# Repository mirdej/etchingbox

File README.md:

# AETZBOX
### DIY Mobile PCB Etching KIT

## The Idea 
Build a portable / mobile PCB etching workstation that fulfills these criteria
* waterproof
* able to etch 100x160mm double sided boards with 8mil precision
* low cost.  total bill of materials should not exceed 150 CHF
* diy approach, mostly laser cut plexi and easily sourceable materials
* fits in a RAKO Box

Some guiding ideas
* use very little but always fresh chemicals 
* good heat management: etching has to be done at 45-50 degrees celsius, developer has to be kept at >20 degrees as well (in my workshop, temperatures can easily drop below 16 degrees and developing is a pain).
* all material and chemicals travel in the box. liquid waste can travel in the box as well until it can properly disposed of.
* should be easy to clean. no electronics exposed to moisture. 
* as few as possible switches and electrical contacts exposed to the harsh etching environment
* self illuminating

## More Info
https://wiki.sgmk-ssam.ch/index.php/EtchingBox

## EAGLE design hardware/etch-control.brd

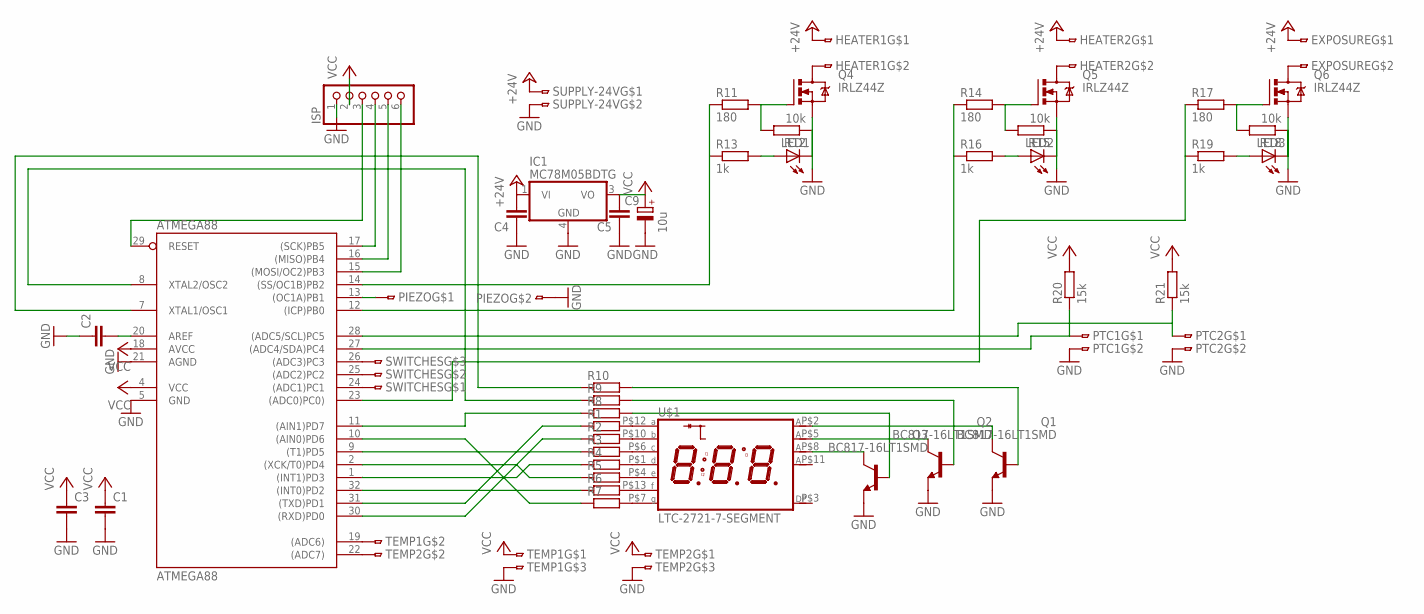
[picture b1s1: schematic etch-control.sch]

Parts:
ATMEGA88: ATMEGA88; TQFP32-08
C1, C2, C3, C4, C5: C-EUC0603; C0603
C9: 10u; CT3528
EXPOSURE: 2PIN-SMD-2.54
HEATER1, HEATER2: 2PIN-SMD-2.54
IC1: MC78M05BDTG; DPACK_3
ISP: PINHD-1X6; 1X06
LED1, LED2, LED3: LED3MM
PIEZO: 2PIN-SMD-2.54
PTC1, PTC2: 2PIN-SMD-2.54
Q1, Q2, Q3: BC817-16LT1SMD; SOT23-BEC
Q4, Q5, Q6: IRLZ44Z; TO220BH
R1, R2, R3, R4, R5, R6, R7, R8, R9, R10: R-EU_R1206; R1206
R11, R14, R17: 180; R1206
R12, R15, R18: 10k; R1206
R13, R16, R19: 1k; R1206
R20, R21: 15k; R1206
SUPPLY-24V: 2PIN-SMD-2.54
SWITCHES: 3PIN-SMD-2.54
TEMP1, TEMP2: 3PIN-SMD-2.54
U$1: LTC-2721-7-SEGMENT; LTC-2721

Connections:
+24V: C4.2, EXPOSURE.2, HEATER1.2, HEATER2.2, IC1.1 (VI), SUPPLY-24V.2
GND: ATMEGA88.5 (GND), ATMEGA88.21 (AGND), C1.2, C2.1, C3.2, C4.1, C5.1, C9.-, IC1.4 (GND), ISP.1, LED1.K (C), LED2.K (C), LED3.K (C), PIEZO.3, PTC1.3, PTC2.3, Q1.E, Q2.E, Q3.E, Q4.S, Q5.S, Q6.S, R12.1, R15.1, R18.1, SUPPLY-24V.3, TEMP1.3, TEMP2.3
MOSI: ATMEGA88.15 ((MOSI/OC2)PB3), ISP.6
unnamed: ATMEGA88.30 ((RXD)PD0), R2.1
unnamed: ATMEGA88.31 ((TXD)PD1), R1.1
unnamed: ATMEGA88.32 ((INT0)PD2), R6.1
unnamed: ATMEGA88.1 ((INT1)PD3), R4.1
unnamed: ATMEGA88.2 ((XCK/T0)PD4), R5.1
unnamed: ATMEGA88.8 (XTAL2/OSC2), R9.1
unnamed: ATMEGA88.7 (XTAL1/OSC1), R10.1
unnamed: ATMEGA88.11 ((AIN1)PD7), R8.1
unnamed: ATMEGA88.9 ((T1)PD5), R3.1
unnamed: R1.2, U$1.P$12 (A)
unnamed: R2.2, U$1.P$10 (B)
unnamed: R3.2, U$1.P$6 (C)
unnamed: R4.2, U$1.P$1 (D)
unnamed: R5.2, U$1.P$4 (E)
unnamed: R6.2, U$1.P$13 (F)
unnamed: R7.2, U$1.P$7 (G)
unnamed: ATMEGA88.29 (RESET), ISP.3
unnamed: ATMEGA88.20 (AREF), C2.2
unnamed: HEATER1.3, Q4.D
unnamed: Q4.G, R11.2, R12.2
unnamed: ATMEGA88.13 ((OC1A)PB1), PIEZO.2
unnamed: ATMEGA88.10 ((AIN0)PD6), R7.1
unnamed: LED1.A, R13.2
unnamed: ATMEGA88.14 ((SS/OC1B)PB2), R11.1, R13.1
unnamed: Q1.B, R10.2
unnamed: Q2.B, R9.2
unnamed: Q3.B, R8.2
unnamed: Q1.C, U$1.P$2 (D1)
unnamed: Q2.C, U$1.P$5 (D2)
unnamed: Q3.C, U$1.P$8 (D3)
unnamed: HEATER2.3, Q5.D
unnamed: Q5.G, R14.2, R15.2
unnamed: LED2.A, R16.2
unnamed: ATMEGA88.12 ((ICP)PB0), R14.1, R16.1
unnamed: EXPOSURE.3, Q6.D
unnamed: Q6.G, R17.2, R18.2
unnamed: LED3.A, R19.2
unnamed: ATMEGA88.16 ((MISO)PB4), ISP.5
unnamed: ATMEGA88.19 ((ADC6)), TEMP1.2
unnamed: ATMEGA88.22 ((ADC7)), TEMP2.2
unnamed: ATMEGA88.27 ((ADC4/SDA)PC4), PTC1.2, R20.1
unnamed: ATMEGA88.23 ((ADC0)PC0)), R17.1, R19.1
unnamed: ATMEGA88.28 ((ADC5/SCL)PC5), PTC2.2, R21.1
unnamed: ATMEGA88.24 ((ADC1)PC1), SWITCHES.1
unnamed: ATMEGA88.25 ((ADC2)PC2), SWITCHES.2
unnamed: ATMEGA88.26 ((ADC3)PC3), SWITCHES.3
SCK: ATMEGA88.17 ((SCK)PB5), ISP.4
VCC: ATMEGA88.4 (VCC), ATMEGA88.18 (AVCC), C1.1, C3.1, C5.2, C9.+, IC1.3 (VO), ISP.2, R20.2, R21.2, TEMP1.1, TEMP2.1

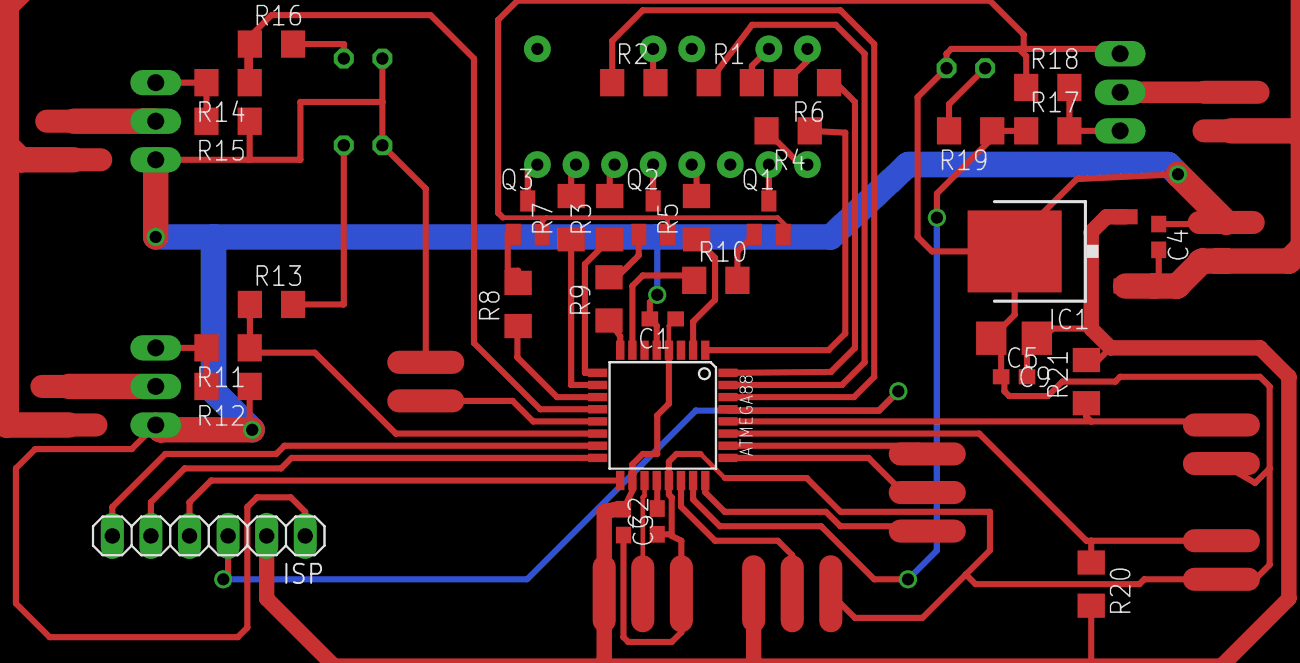
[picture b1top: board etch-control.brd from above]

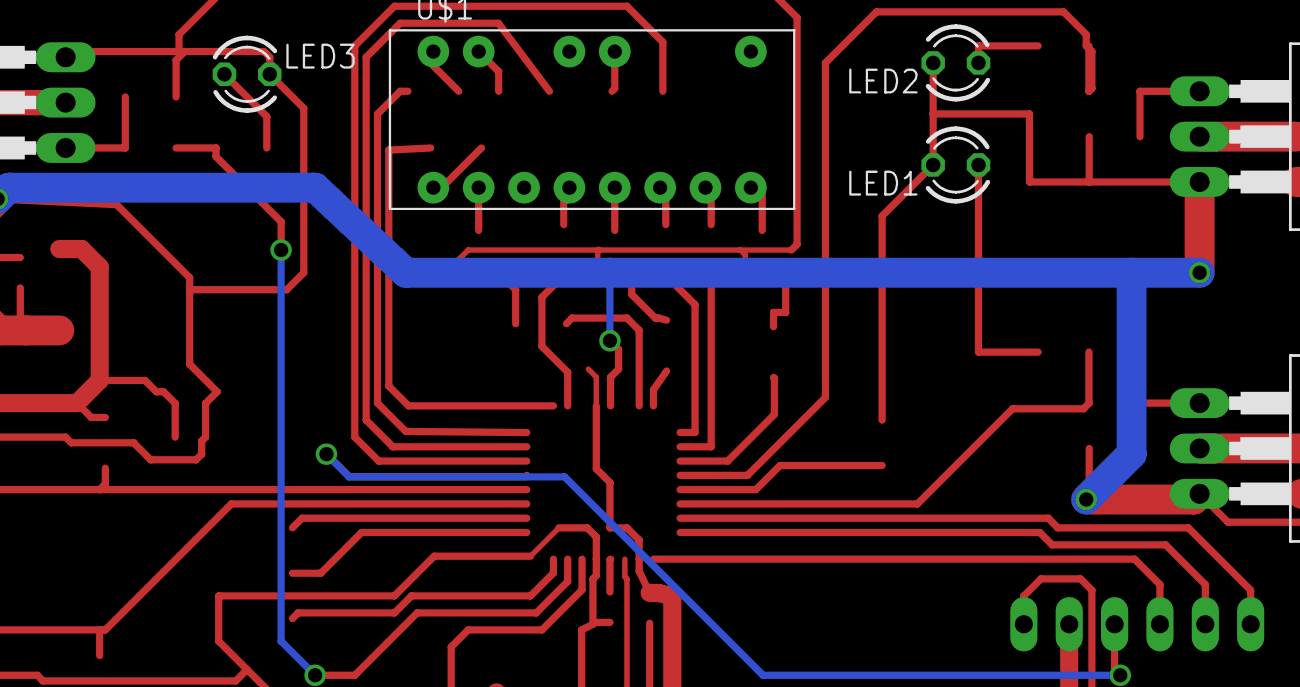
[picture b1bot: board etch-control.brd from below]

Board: 2 copper layers, 50 parts (7 on the bottom side), 51 nets.

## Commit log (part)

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2014-05-13 added readme
2014-05-13 redme
2014-05-13 added first version of controler pcb and firmware
2014-05-13 basic heater control
2018-11-13 make place for completely new version
2018-11-16 new approach
2018-11-16 change mosfets, smaller borad
2018-11-26 Basic fuctions
2018-11-26 add sketchup models
2018-11-29 new bubble unit, holes for china plugs
2018-11-30 new basin holder
2018-11-30 4mm smaller lightpad.
2018-11-30 correct uv height. lighter lid, text
2018-11-30 some corrections
2018-12-01 fix missing link
2018-12-02 small corrections to holes. logo
2018-12-02 forgot to add logo.h
2018-12-03 pimped display
2018-12-03 workshop photos
2018-12-04 some minor hardware corrections during workshop. seperate logos. merge display code by dusjagr. add ambient temperatur display
2018-12-04 add lid holder
2019-01-21 full stop uv when finished flashing. no ramp down
2019-02-08 add more sounds, temperature log option, safety check
2019-02-08 try pulsing airpump
2019-02-08 Using SAMD Timer 4 as slow PWM (crude way) to prevent whining of air pump
2019-02-09 add bath temperture rise safety checks
2019-02-11 prevent slow heat rate error when bath is warm)
2019-02-16 add new version of ub leds that should cover whole board
2021-07-26 stash latest version with MKR-Wifi before changing to ESP32
2021-07-26 esp3 version
2022-04-10 add esp32 firmware
2025-04-17 remove 2018 version
2025-04-17 2025 version hardware
2025-04-17 rm old firmware
2025-04-17 rm hardware 2018
2025-04-17 redme typos
2025-04-17 firmware version workshop april
2025-04-17 corret resistor value
2025-04-17 add bom for uv led boards
2025-04-17 add bom
2025-04-17 Add sketch
2025-04-17 Add dark image
2025-05-17 disable waterlevel sensor !!!
2025-08-05 add besteck
